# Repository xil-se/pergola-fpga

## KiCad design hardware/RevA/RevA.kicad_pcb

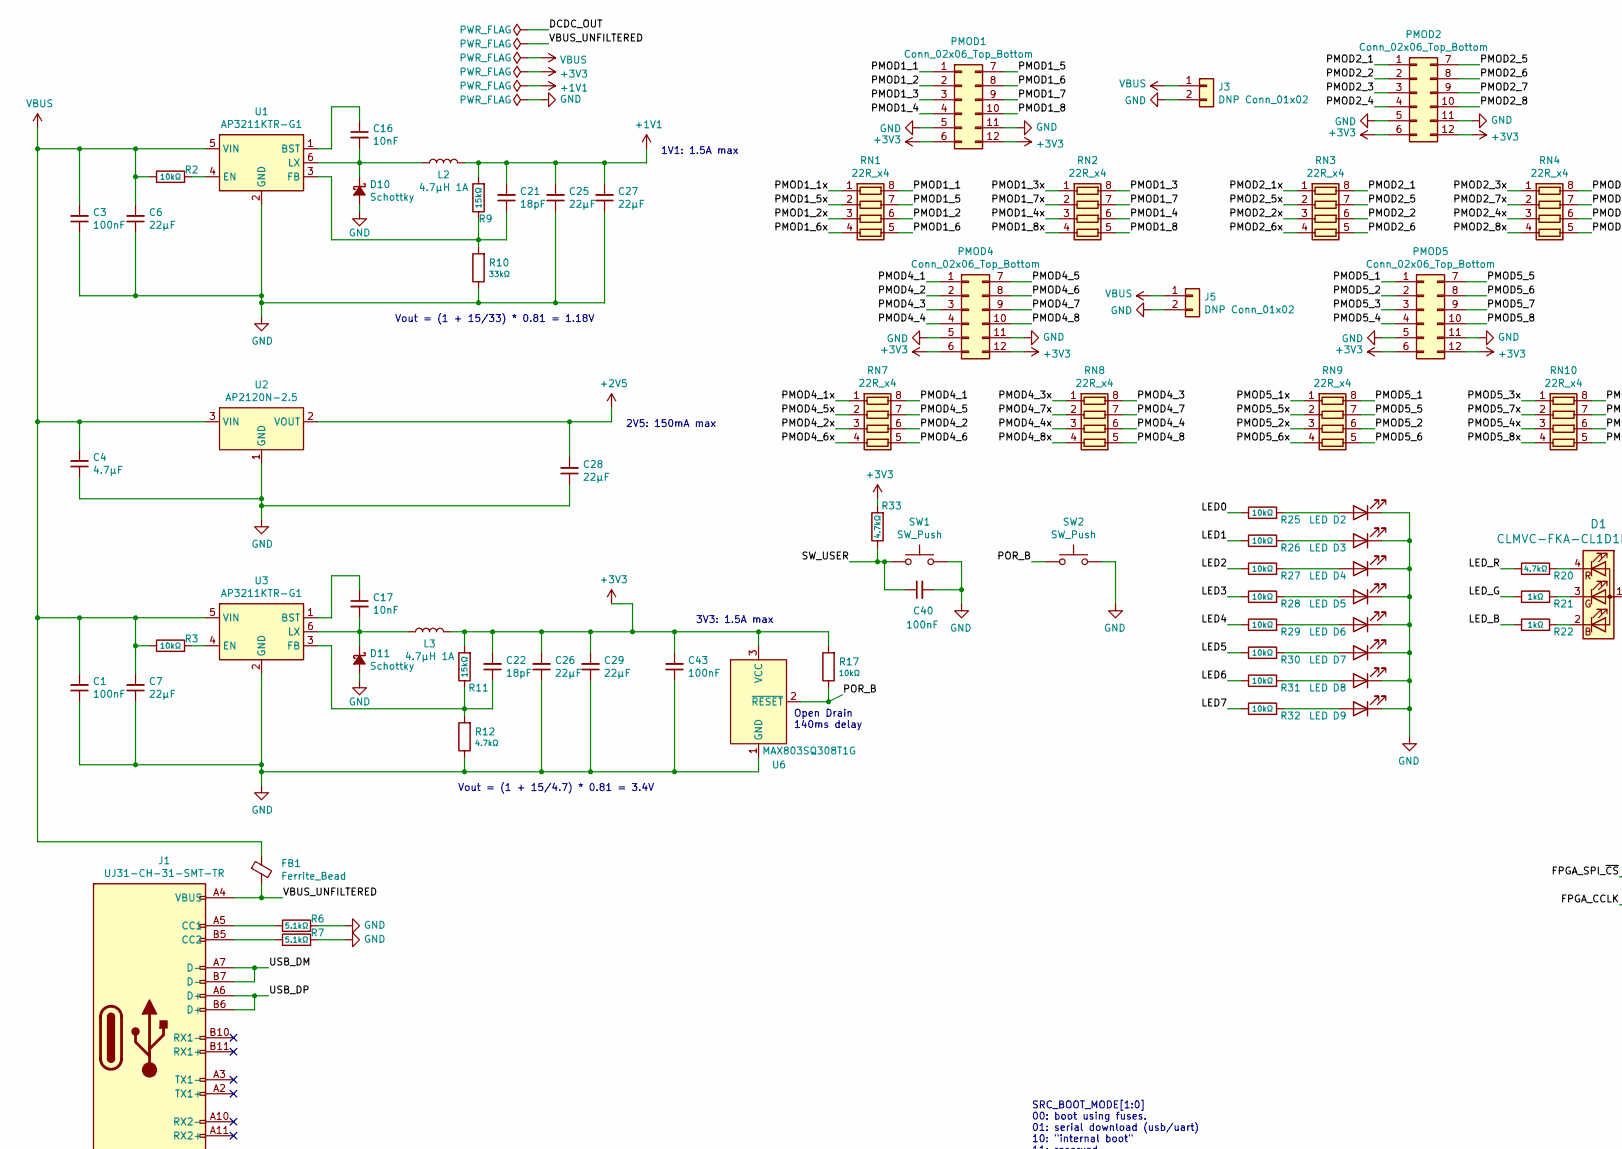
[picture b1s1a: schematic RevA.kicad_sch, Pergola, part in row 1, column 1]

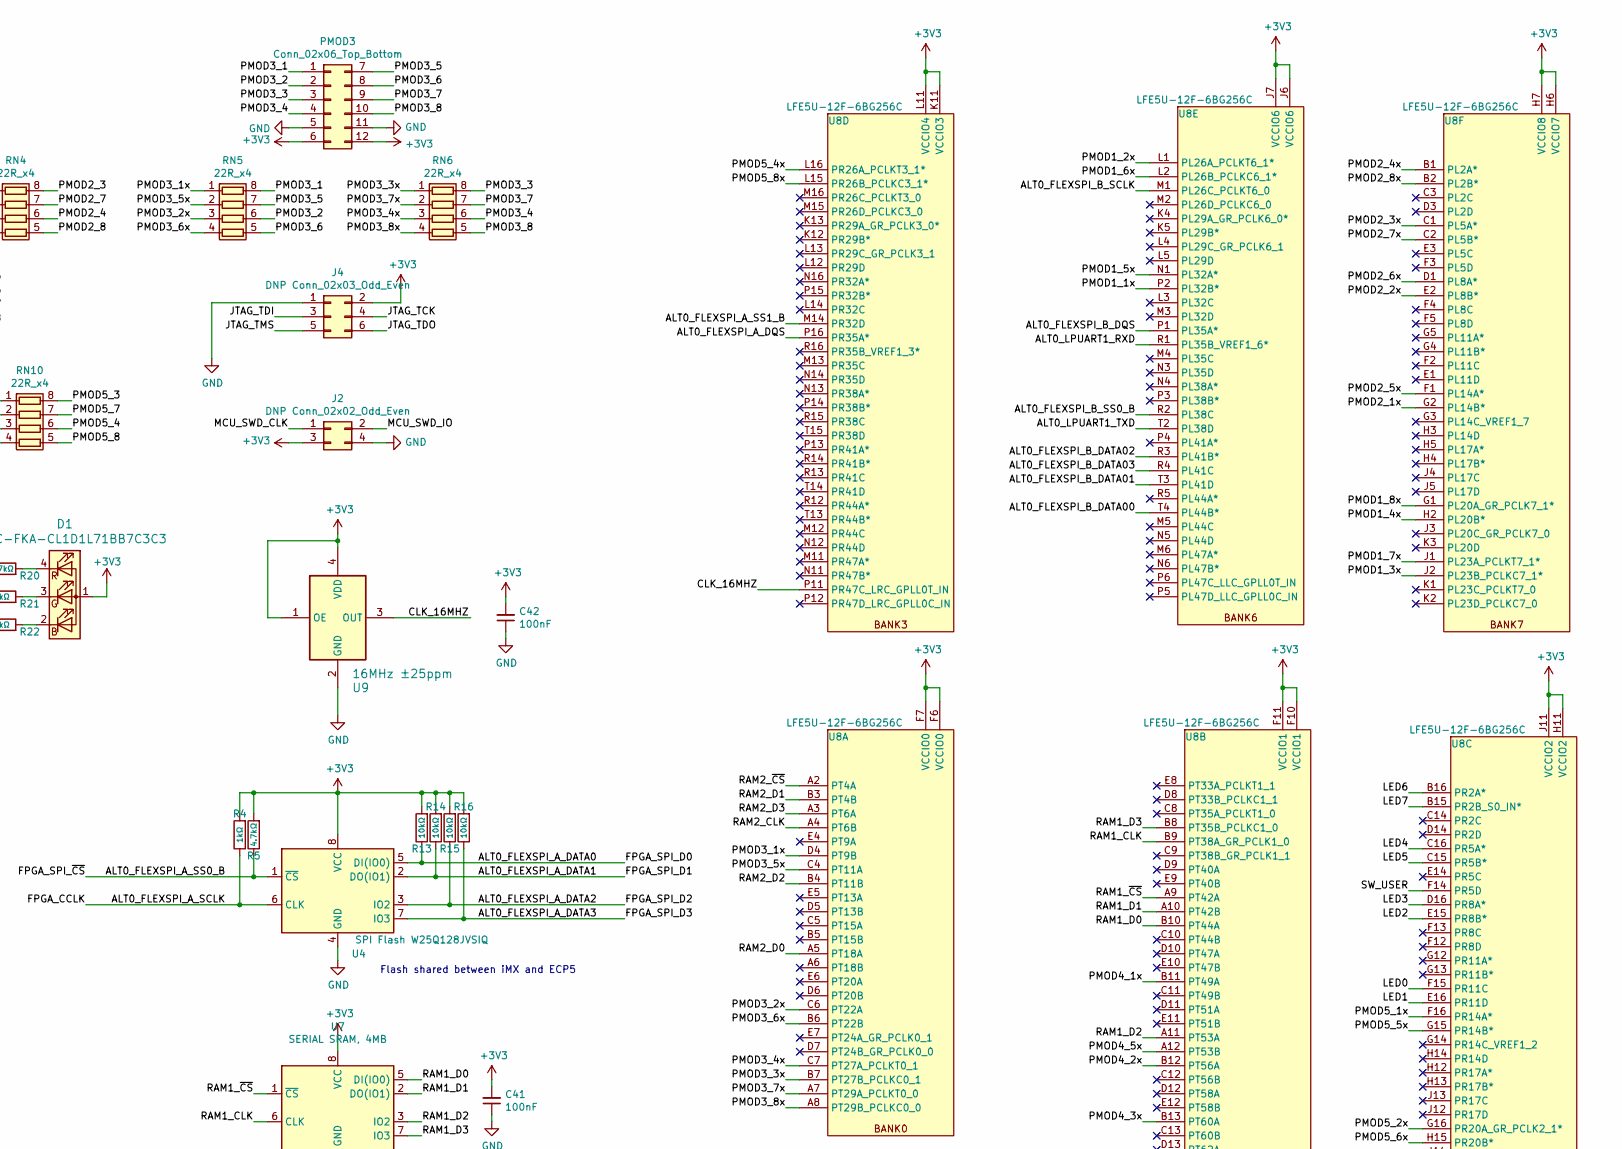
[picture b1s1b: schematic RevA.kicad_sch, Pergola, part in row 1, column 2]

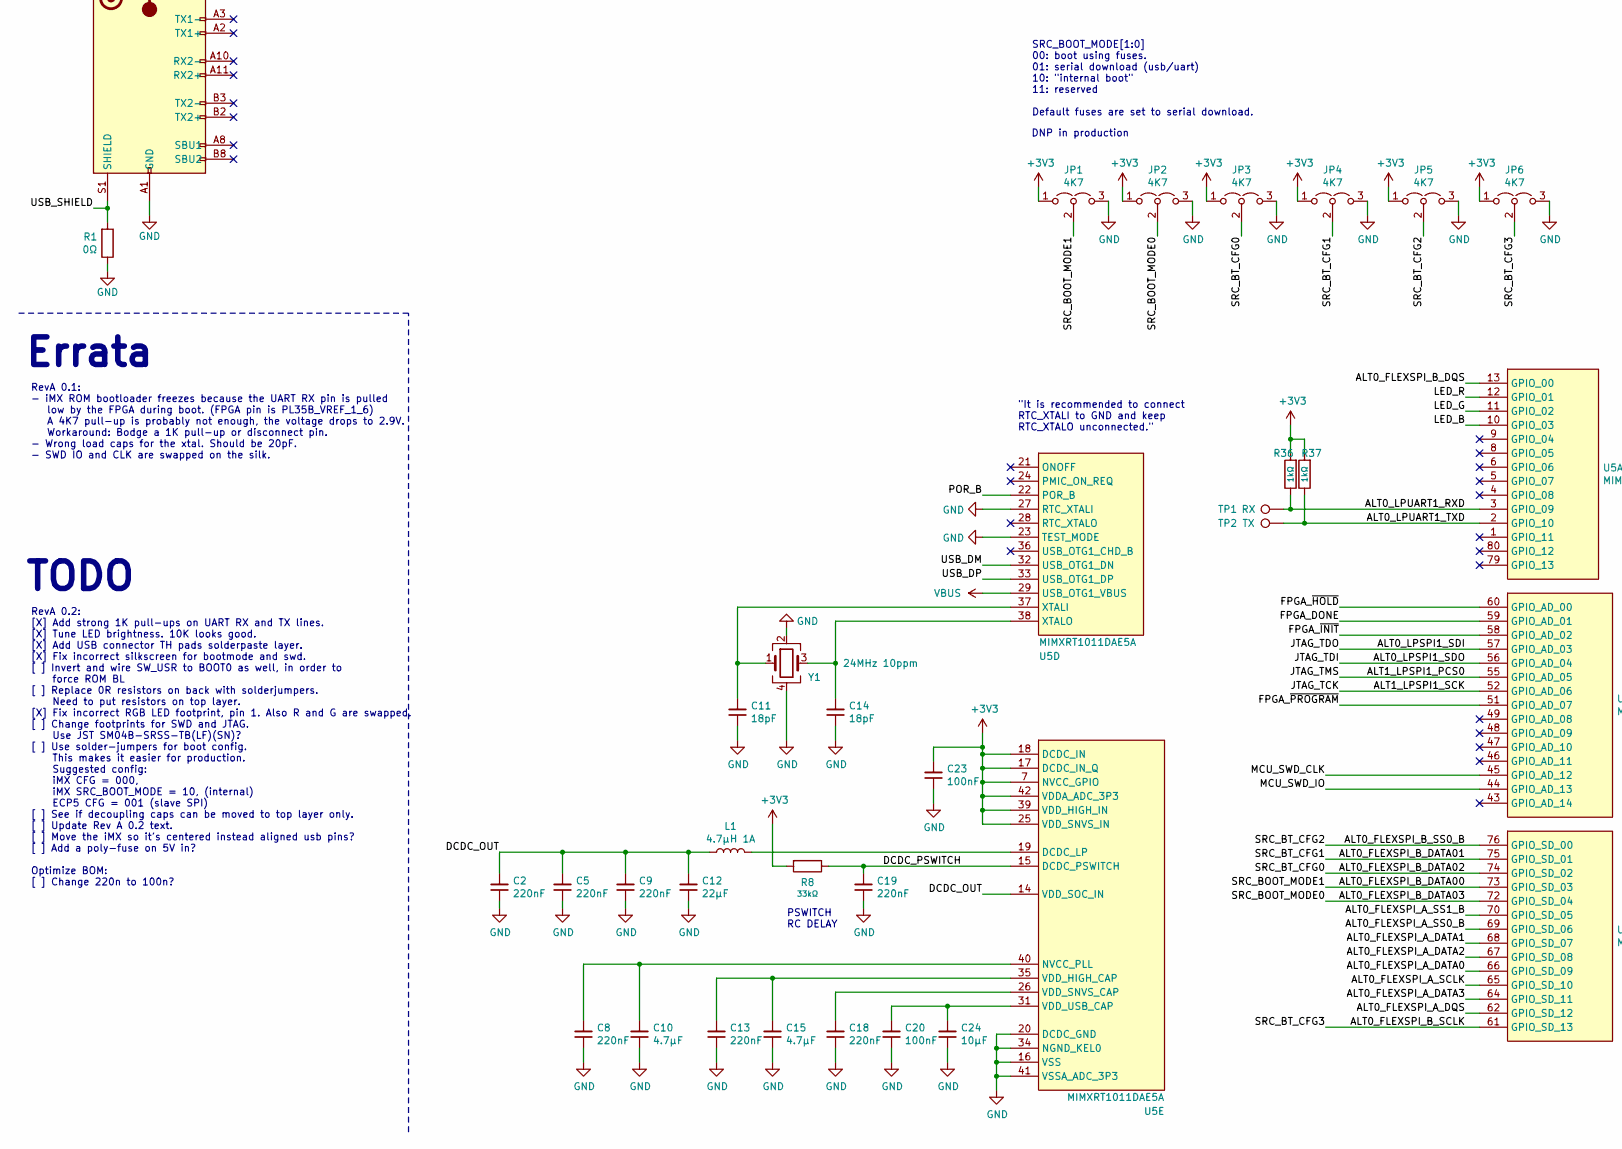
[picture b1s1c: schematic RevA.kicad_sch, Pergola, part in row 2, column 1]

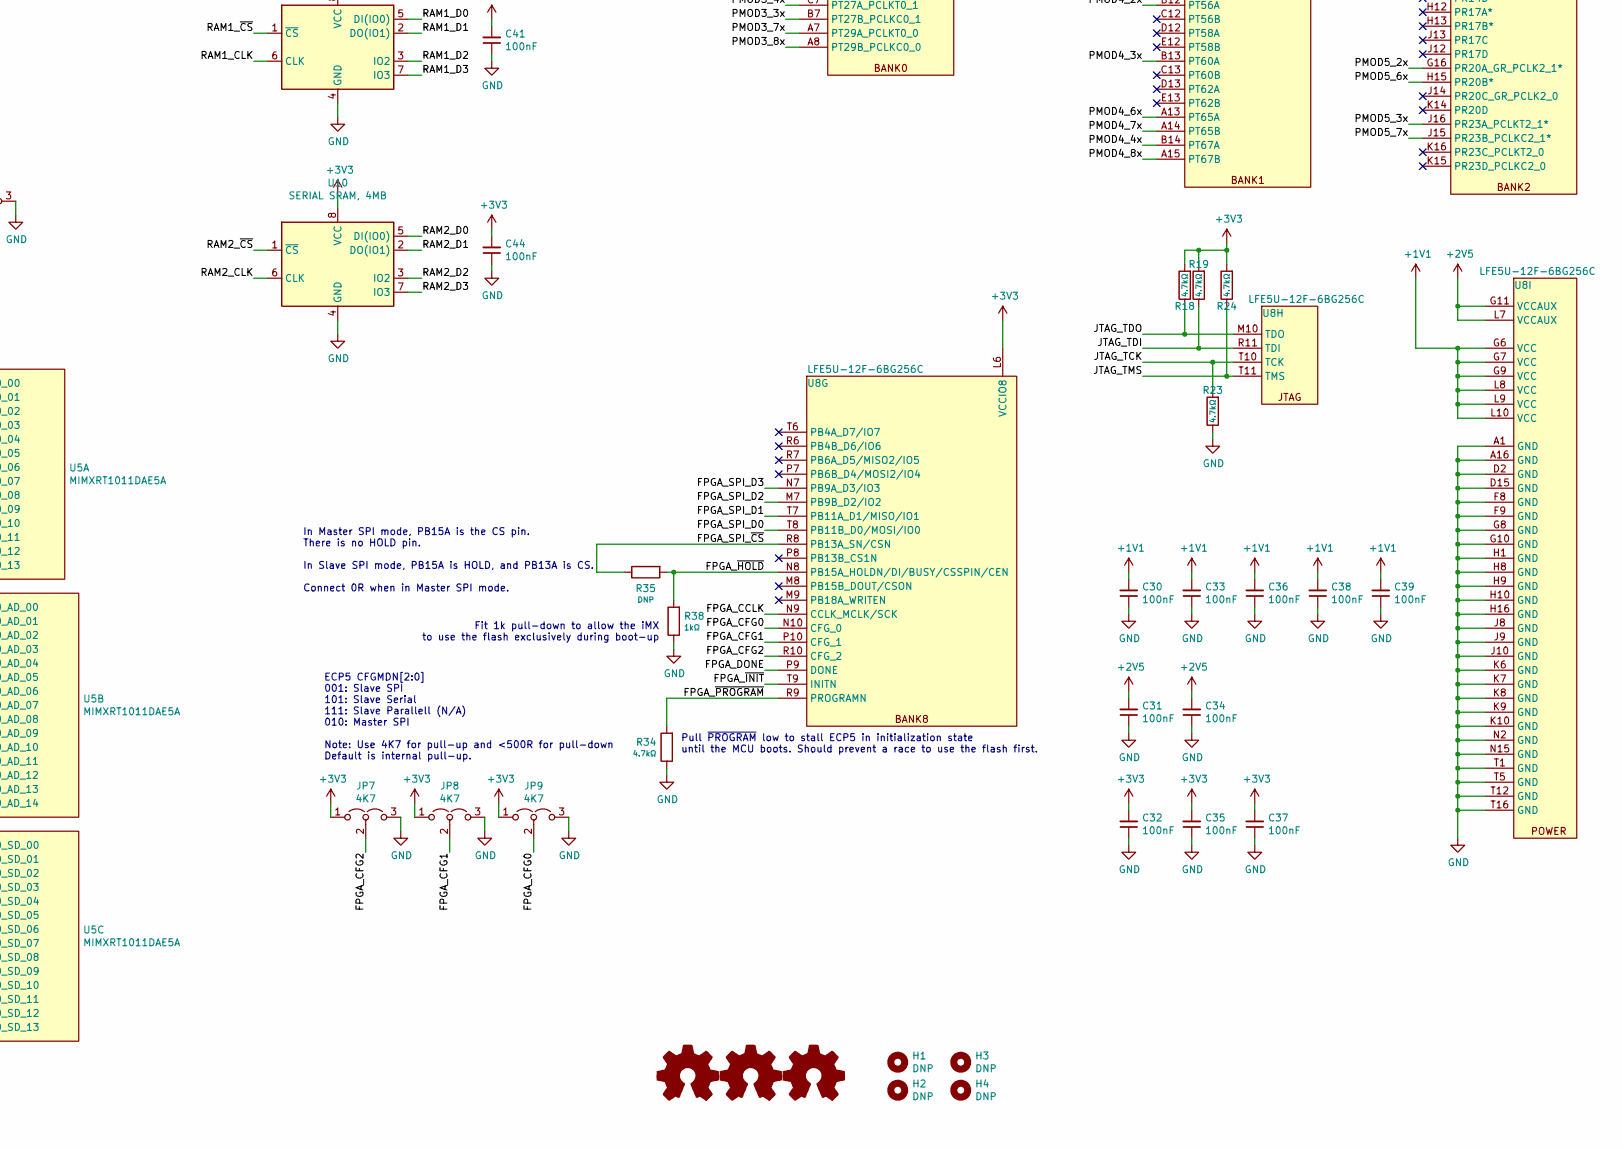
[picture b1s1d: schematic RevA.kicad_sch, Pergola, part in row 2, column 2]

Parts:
C1, C3, C20, C23, C30, C31, C32, C33, C34, C35, C36, C37, C38, C39, C40, C41, C42, C43, C44: 100nF; C_0402_1005Metric
C2, C5, C8, C9, C13, C18, C19: 220nF; C_0402_1005Metric
C4, C10, C15: 4.7µF; C_0402_1005Metric
C6, C7, C12, C25, C26, C27, C28, C29: 22µF; C_0805_2012Metric; Digikey 490-GRM219R61C226ME15KCT-ND
C11, C14, C21, C22: 18pF; C_0402_1005Metric
C16, C17: 10nF; C_0402_1005Metric
C24: 10µF; C_0402_1005Metric
D1: CLMVC-FKA-CL1D1L71BB7C3C3; LED_Cree-PLCC4_2x2mm_CW; Mouser 941-CLMVCFKACL1D1L71
D2, D3, D4, D5, D6, D7, D8, D9: LED; LED_0603_1608Metric; Digikey 732-4978-1-ND
D10, D11: Schottky; D_SOD-323F; Digikey 1727-3852-1-ND
FB1: Ferrite_Bead; L_0805_2012Metric; Digikey 490-5987-1-ND
H1, H2, H3, H4: DNP; MountingHole_3.5mm
J1: UJ31-CH-31-SMT-TR; CUI_UJ31-CH-312-SMT-TR; Digikey 102-4485-1-ND
J2: DNP Conn_02x02_Odd_Even; PinHeader_2x02_P2.54mm_Vertical_SMD
J3, J5: DNP Conn_01x02; PinSocket_1x02_P2.54mm_Vertical
J4: DNP Conn_02x03_Odd_Even; PinHeader_2x03_P2.54mm_Vertical_SMD
JP1, JP2, JP3, JP4, JP5, JP6, JP7, JP8, JP9: 4K7; JP_3_0402_1005Metric
L1, L2, L3: 4.7µH 1A; L_1008_1210; Digikey 490-18407-1-ND
LOGO1: Logo_Open_Hardware_Small; OSHW-Logo_5.7x6mm_SilkScreen
LOGO2: Logo_Open_Hardware_Small; logo
LOGO3: Logo_Open_Hardware_Small; xil_logo_new
PMOD1, PMOD2, PMOD3, PMOD4, PMOD5: Conn_02x06_Top_Bottom; PMOD_Socket_2x06_P2.54mm_Horizontal; Digikey SAM1224-06-ND
R1: 0Ω; R_0402_1005Metric
R2, R3, R13, R14, R15, R16, R17, R25, R26, R27, R28, R29, R30, R31, R32: 10kΩ; R_0402_1005Metric
R4, R21, R22, R36, R37, R38: 1kΩ; R_0402_1005Metric
R5, R12, R18, R19, R20, R23, R24, R33, R34: 4.7kΩ; R_0402_1005Metric
R6, R7: 5.1kΩ; R_0402_1005Metric
R8, R10: 33kΩ; R_0402_1005Metric
R9, R11: 15kΩ; R_0402_1005Metric
R35: DNP; R_0402_1005Metric
RN1, RN2, RN3, RN4, RN5, RN6, RN7, RN8, RN9, RN10: 22R_x4; R_Array_Convex_4x0402; Digikey Y7220CT-ND
SW1, SW2: SW_Push; SW_SPST_FSMSM; Digikey CKN12329-1-ND
TP1: RX; TestPoint_Pad_D1.0mm
TP2: TX; TestPoint_Pad_D1.0mm
U1, U3: AP3211KTR-G1; SOT-23-6; Digikey AP3211KTR-G1DICT-ND
U2: AP2120N-2.5; SOT-23; Digikey AP2120N-2.5TRG1DICT-ND
U4: SPI Flash W25Q128JVSIQ; SOA008-150-208mil; Digikey W25Q128JVSIQCT-ND
U5: MIMXRT1011DAE5A; LQFP-80_12x12mm_P0.5mm; Digikey 568-MIMXRT1011DAE5A-ND
U6: MAX803SQ308T1G; SOT-323_SC-70; Digikey MAX803SQ308T1GOSCT-ND
U7, U10: SERIAL SRAM, 4MB; SOIC-8_3.9x4.9mm_P1.27mm; Mouser 870-62WS5128FBLL2NIT
U8: LFE5U-12F-6BG256C; cabga256; Mouser 842-LFE5U12F6BG256C
U9: 16MHz ±25ppm; Crystal_SMD_3225-4Pin_3.2x2.5mm; Mouser 520-3225MV-160-CNT
Y1: 24MHz 10ppm; Crystal_SMD_3225-4Pin_3.2x2.5mm; Mouser 732-TX325-24F20G-AC3

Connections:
+1V1: C21.2, C25.2, C27.2, C30.2, C33.2, C36.2, C38.2, C39.2, L2.2, R9.2, U8.G6 (VCC), U8.G7 (VCC), U8.G9 (VCC), U8.L8 (VCC), U8.L9 (VCC), U8.L10 (VCC)
+2V5: C28.2, C31.2, C34.2, U2.2 (VOUT), U8.G11 (VCCAUX), U8.L7 (VCCAUX)
+3V3: C22.2, C23.2, C26.2, C29.2, C32.2, C35.2, C37.2, C41.2, C42.2, C43.2, C44.2, D1.1 (A), J2.3, J4.2, JP1.1 (A), JP2.1 (A), JP3.1 (A), JP4.1 (A), JP5.1 (A), JP6.1 (A), JP7.1 (A), JP8.1 (A), JP9.1 (A), L3.2, PMOD1.6, PMOD1.12, PMOD2.6, PMOD2.12, PMOD3.6, PMOD3.12, PMOD4.6, PMOD4.12, PMOD5.6, PMOD5.12, R4.2, R5.2, R8.2, R11.2, R13.2, R14.2, R15.2, R16.2, R17.2, R18.2, R19.2, R24.2, R33.2, R36.2, R37.2, U4.8 (VCC), U5.7 (NVCC_GPIO), U5.17 (DCDC_IN_Q), U5.18 (DCDC_IN), U5.25 (VDD_SNVS_IN), U5.39 (VDD_HIGH_IN), U5.42 (VDDA_ADC_3P3), U5.50 (NVCC_GPIO), U5.63 (NVCC_GPIO), U5.71 (NVCC_GPIO), U6.3 (VCC), U7.8 (VCC), U8.F6 (VCCIO0), U8.F7 (VCCIO0), U8.F10 (VCCIO1), U8.F11 (VCCIO1), U8.H6 (VCCIO7), U8.H7 (VCCIO8), U8.H11 (VCCIO2), U8.J6 (VCCIO6), U8.J7 (VCCIO6), U8.J11 (VCCIO2), U8.K11 (VCCIO3), U8.L6 (VCCIO8), U8.L11 (VCCIO4), U9.1 (OE), U9.4 (VDD), U10.8 (VCC)
/ALT0_FLEXSPI_A_DATA0: R13.1, U4.5 (DI(IO0)), U5.66 (GPIO_SD_09), U8.T8 (PB11B_D0/MOSI/IO0)
/ALT0_FLEXSPI_A_DATA1: R14.1, U4.2 (DO(IO1)), U5.68 (GPIO_SD_07), U8.T7 (PB11A_D1/MISO/IO1)
/ALT0_FLEXSPI_A_DATA2: R15.1, U4.3 (IO2), U5.67 (GPIO_SD_08), U8.M7 (PB9B_D2/IO2)
/ALT0_FLEXSPI_A_DATA3: R16.1, U4.7 (IO3), U5.64 (GPIO_SD_11), U8.N7 (PB9A_D3/IO3)
/ALT0_FLEXSPI_A_DQS: U5.62 (GPIO_SD_12), U8.P16 (PR35A*)
/ALT0_FLEXSPI_A_SCLK: R4.1, U4.6 (CLK), U5.65 (GPIO_SD_10), U8.N9 (CCLK_MCLK/SCK)
/ALT0_FLEXSPI_A_SS0_B: R5.1, R35.1, U4.1 (~CS), U5.69 (GPIO_SD_06), U8.R8 (PB13A_SN/CSN)
/ALT0_FLEXSPI_A_SS1_B: U5.70 (GPIO_SD_05), U8.M14 (PR32D)
/ALT0_FLEXSPI_B_DATA00: JP1.2 (C), U5.73 (GPIO_SD_03), U8.T4 (PL44B*)
/ALT0_FLEXSPI_B_DATA01: JP4.2 (C), U5.75 (GPIO_SD_01), U8.T3 (PL41D)
/ALT0_FLEXSPI_B_DATA02: JP3.2 (C), U5.74 (GPIO_SD_02), U8.R3 (PL41B*)
/ALT0_FLEXSPI_B_DATA03: JP2.2 (C), U5.72 (GPIO_SD_04), U8.R4 (PL41C)
/ALT0_FLEXSPI_B_DQS: U5.13 (GPIO_00), U8.P1 (PL35A*)
/ALT0_FLEXSPI_B_SCLK: JP6.2 (C), U5.61 (GPIO_SD_13), U8.M1 (PL26C_PCLKT6_0)
/ALT0_FLEXSPI_B_SS0_B: JP5.2 (C), U5.76 (GPIO_SD_00), U8.R2 (PL38C)
/ALT0_LPSPI1_SDI: J4.6, R18.1, U5.57 (GPIO_AD_03), U8.M10 (TDO)
/ALT0_LPSPI1_SDO: J4.3, R19.1, U5.56 (GPIO_AD_04), U8.R11 (TDI)
/ALT0_LPUART1_RXD: R36.1, TP1.1, U5.3 (GPIO_09), U8.R1 (PL35B_VREF1_6*)
/ALT0_LPUART1_TXD: R37.1, TP2.1, U5.2 (GPIO_10), U8.T2 (PL38D)
/ALT1_LPSPI1_PCS0: J4.5, R24.1, U5.55 (GPIO_AD_05), U8.T11 (TMS)
/ALT1_LPSPI1_SCK: J4.4, R23.2, U5.52 (GPIO_AD_06), U8.T10 (TCK)
/CLK_16MHZ: U8.P11 (PR47C_LRC_GPLL0T_IN), U9.3 (OUT)
/DCDC_OUT: C2.2, C5.2, C9.2, C12.2, L1.1, U5.14 (VDD_SOC_IN), U5.53 (VDD_SOC_IN), U5.77 (VDD_SOC_IN)
/DCDC_PSWITCH: C19.2, R8.1, U5.15 (DCDC_PSWITCH)
/FPGA_CFG0: JP9.2 (C), U8.N10 (CFG_0)
/FPGA_CFG1: JP8.2 (C), U8.P10 (CFG_1)
/FPGA_CFG2: JP7.2 (C), U8.R10 (CFG_2)
/FPGA_DONE: U5.59 (GPIO_AD_01), U8.P9 (DONE)
/FPGA_~HOLD: R35.2, R38.2, U5.60 (GPIO_AD_00), U8.N8 (PB15A_HOLDN/DI/BUSY/CSSPIN/CEN)
/FPGA_~INIT: U5.58 (GPIO_AD_02), U8.T9 (INITN)
/FPGA_~PROGRAM: R34.2, U5.51 (GPIO_AD_07), U8.R9 (PROGRAMN)
/LED0: R25.1, U8.F15 (PR11C)
/LED1: R26.1, U8.E16 (PR11D)
/LED2: R27.1, U8.E15 (PR8B*)
/LED3: R28.1, U8.D16 (PR8A*)
/LED4: R29.1, U8.C16 (PR5A*)
/LED5: R30.1, U8.C15 (PR5B*)
/LED6: R31.1, U8.B16 (PR2A*)
/LED7: R32.1, U8.B15 (PR2B_S0_IN*)
/LED_B: R22.1, U5.10 (GPIO_03)
/LED_G: R21.1, U5.11 (GPIO_02)
/LED_R: R20.1, U5.12 (GPIO_01)
/MCU_SWD_CLK: J2.1, U5.45 (GPIO_AD_12)
/MCU_SWD_IO: J2.2, U5.44 (GPIO_AD_13)
/PMOD1_1: PMOD1.1, RN1.8 (R1.2)
/PMOD1_1x: RN1.1 (R1.1), U8.P2 (PL32B*)
/PMOD1_2: PMOD1.2, RN1.6 (R3.2)
/PMOD1_2x: RN1.3 (R3.1), U8.L1 (PL26A_PCLKT6_1*)
/PMOD1_3: PMOD1.3, RN2.8 (R1.2)
/PMOD1_3x: RN2.1 (R1.1), U8.J2 (PL23B_PCLKC7_1*)
/PMOD1_4: PMOD1.4, RN2.6 (R3.2)
/PMOD1_4x: RN2.3 (R3.1), U8.H2 (PL20B*)
/PMOD1_5: PMOD1.7, RN1.7 (R2.2)
/PMOD1_5x: RN1.2 (R2.1), U8.N1 (PL32A*)
/PMOD1_6: PMOD1.8, RN1.5 (R4.2)
/PMOD1_6x: RN1.4 (R4.1), U8.L2 (PL26B_PCLKC6_1*)
/PMOD1_7: PMOD1.9, RN2.7 (R2.2)
/PMOD1_7x: RN2.2 (R2.1), U8.J1 (PL23A_PCLKT7_1*)
/PMOD1_8: PMOD1.10, RN2.5 (R4.2)
/PMOD1_8x: RN2.4 (R4.1), U8.G1 (PL20A_GR_PCLK7_1*)
/PMOD2_1: PMOD2.1, RN3.8 (R1.2)
/PMOD2_1x: RN3.1 (R1.1), U8.G2 (PL14B*)
/PMOD2_2: PMOD2.2, RN3.6 (R3.2)
/PMOD2_2x: RN3.3 (R3.1), U8.E2 (PL8B*)
/PMOD2_3: PMOD2.3, RN4.8 (R1.2)
/PMOD2_3x: RN4.1 (R1.1), U8.C1 (PL5A*)
/PMOD2_4: PMOD2.4, RN4.6 (R3.2)
/PMOD2_4x: RN4.3 (R3.1), U8.B1 (PL2A*)
/PMOD2_5: PMOD2.7, RN3.7 (R2.2)
/PMOD2_5x: RN3.2 (R2.1), U8.F1 (PL14A*)
/PMOD2_6: PMOD2.8, RN3.5 (R4.2)
/PMOD2_6x: RN3.4 (R4.1), U8.D1 (PL8A*)
/PMOD2_7: PMOD2.9, RN4.7 (R2.2)
/PMOD2_7x: RN4.2 (R2.1), U8.C2 (PL5B*)
/PMOD2_8: PMOD2.10, RN4.5 (R4.2)
/PMOD2_8x: RN4.4 (R4.1), U8.B2 (PL2B*)
/PMOD3_1: PMOD3.1, RN5.8 (R1.2)
/PMOD3_1x: RN5.1 (R1.1), U8.D4 (PT9B)
/PMOD3_2: PMOD3.2, RN5.6 (R3.2)
/PMOD3_2x: RN5.3 (R3.1), U8.C6 (PT22A)
/PMOD3_3: PMOD3.3, RN6.8 (R1.2)
/PMOD3_3x: RN6.1 (R1.1), U8.B7 (PT27B_PCLKC0_1)
/PMOD3_4: PMOD3.4, RN6.6 (R3.2)
/PMOD3_4x: RN6.3 (R3.1), U8.C7 (PT27A_PCLKT0_1)
/PMOD3_5: PMOD3.7, RN5.7 (R2.2)
/PMOD3_5x: RN5.2 (R2.1), U8.C4 (PT11A)
/PMOD3_6: PMOD3.8, RN5.5 (R4.2)
/PMOD3_6x: RN5.4 (R4.1), U8.B6 (PT22B)
/PMOD3_7: PMOD3.9, RN6.7 (R2.2)
/PMOD3_7x: RN6.2 (R2.1), U8.A7 (PT29A_PCLKT0_0)
/PMOD3_8: PMOD3.10, RN6.5 (R4.2)
/PMOD3_8x: RN6.4 (R4.1), U8.A8 (PT29B_PCLKC0_0)
/PMOD4_1: PMOD4.1, RN7.8 (R1.2)
/PMOD4_1x: RN7.1 (R1.1), U8.B11 (PT49A)
/PMOD4_2: PMOD4.2, RN7.6 (R3.2)
/PMOD4_2x: RN7.3 (R3.1), U8.B12 (PT56A)
/PMOD4_3: PMOD4.3, RN8.8 (R1.2)
/PMOD4_3x: RN8.1 (R1.1), U8.B13 (PT60A)
/PMOD4_4: PMOD4.4, RN8.6 (R3.2)
/PMOD4_4x: RN8.3 (R3.1), U8.B14 (PT67A)
/PMOD4_5: PMOD4.7, RN7.7 (R2.2)
/PMOD4_5x: RN7.2 (R2.1), U8.A12 (PT53B)
/PMOD4_6: PMOD4.8, RN7.5 (R4.2)
/PMOD4_6x: RN7.4 (R4.1), U8.A13 (PT65A)
/PMOD4_7: PMOD4.9, RN8.7 (R2.2)
/PMOD4_7x: RN8.2 (R2.1), U8.A14 (PT65B)
/PMOD4_8: PMOD4.10, RN8.5 (R4.2)
/PMOD4_8x: RN8.4 (R4.1), U8.A15 (PT67B)
/PMOD5_1: PMOD5.1, RN9.8 (R1.2)
/PMOD5_1x: RN9.1 (R1.1), U8.F16 (PR14A*)
/PMOD5_2: PMOD5.2, RN9.6 (R3.2)
/PMOD5_2x: RN9.3 (R3.1), U8.G16 (PR20A_GR_PCLK2_1*)
/PMOD5_3: PMOD5.3, RN10.8 (R1.2)
/PMOD5_3x: RN10.1 (R1.1), U8.J16 (PR23A_PCLKT2_1*)
/PMOD5_4: PMOD5.4, RN10.6 (R3.2)
/PMOD5_4x: RN10.3 (R3.1), U8.L16 (PR26A_PCLKT3_1*)
/PMOD5_5: PMOD5.7, RN9.7 (R2.2)
/PMOD5_5x: RN9.2 (R2.1), U8.G15 (PR14B*)
/PMOD5_6: PMOD5.8, RN9.5 (R4.2)
/PMOD5_6x: RN9.4 (R4.1), U8.H15 (PR20B*)
/PMOD5_7: PMOD5.9, RN10.7 (R2.2)
/PMOD5_7x: RN10.2 (R2.1), U8.J15 (PR23B_PCLKC2_1*)
/PMOD5_8: PMOD5.10, RN10.5 (R4.2)
/PMOD5_8x: RN10.4 (R4.1), U8.L15 (PR26B_PCLKC3_1*)
/POR_B: R17.1, SW2.1, U5.22 (POR_B), U6.2 (~RESET~)
/RAM1_CLK: U7.6 (CLK), U8.B9 (PT38A_GR_PCLK1_0)
/RAM1_D0: U7.5 (DI(IO0)), U8.B10 (PT44A)
/RAM1_D1: U7.2 (DO(IO1)), U8.A10 (PT42B)
/RAM1_D2: U7.3 (IO2), U8.A11 (PT53A)
/RAM1_D3: U7.7 (IO3), U8.B8 (PT35B_PCLKC1_0)
/RAM1_~CS~: U7.1 (~CS), U8.A9 (PT42A)
/RAM2_CLK: U8.A4 (PT6B), U10.6 (CLK)
/RAM2_D0: U8.A5 (PT18A), U10.5 (DI(IO0))
/RAM2_D1: U8.B3 (PT4B), U10.2 (DO(IO1))
/RAM2_D2: U8.B4 (PT11B), U10.3 (IO2)
/RAM2_D3: U8.A3 (PT6A), U10.7 (IO3)
/RAM2_~CS~: U8.A2 (PT4A), U10.1 (~CS)
/SW_USER: C40.1, R33.1, SW1.1, U8.F14 (PR5D)
/USB_DM: J1.A7 (D-), J1.B7 (D-), U5.32 (USB_OTG1_DN)
/USB_DP: J1.A6 (D+), J1.B6 (D+), U5.33 (USB_OTG1_DP)
/USB_SHIELD: J1.S1 (SHIELD), R1.2
/VBUS_UNFILTERED: FB1.2, J1.A4 (VBUS), J1.A9 (VBUS), J1.B4 (VBUS), J1.B9 (VBUS)
GND: C1.1, C2.1, C3.1, C4.1, C5.1, C6.1, C7.1, C8.1, C9.1, C10.1, C11.1, C12.1, C13.1, C14.1, C15.1, C18.1, C19.1, C20.1, C23.1, C24.1, C25.1, C26.1, C27.1, C28.1, C29.1, C30.1, C31.1, C32.1, C33.1, C34.1, C35.1, C36.1, C37.1, C38.1, C39.1, C40.2, C41.1, C42.1, C43.1, C44.1, D2.1 (K), D3.1 (K), D4.1 (K), D5.1 (K), D6.1 (K), D7.1 (K), D8.1 (K), D9.1 (K), D10.2 (A), D11.2 (A), J1.A1 (GND), J1.A12 (GND), J1.B1 (GND), J1.B12 (GND), J2.4, J3.2, J4.1, J5.2, JP1.3 (B), JP2.3 (B), JP3.3 (B), JP4.3 (B), JP5.3 (B), JP6.3 (B), JP7.3 (B), JP8.3 (B), JP9.3 (B), PMOD1.5, PMOD1.11, PMOD2.5, PMOD2.11, PMOD3.5, PMOD3.11, PMOD4.5, PMOD4.11, PMOD5.5, PMOD5.11, R1.1, R6.2, R7.2, R10.1, R12.1, R23.1, R34.1, R38.1, SW1.2, SW2.2, U1.2 (GND), U2.1 (GND), U3.2 (GND), U4.4 (GND), U5.16 (VSS), U5.20 (DCDC_GND), U5.23 (TEST_MODE), U5.27 (RTC_XTALI), U5.30 (VSS), U5.34 (NGND_KEL0), U5.41 (VSSA_ADC_3P3), U5.54 (VSS), U5.78 (VSS), U6.1 (GND), U7.4 (GND), U8.A1 (GND), U8.A16 (GND), U8.D2 (GND), U8.D15 (GND), U8.F8 (GND), U8.F9 (GND), U8.G8 (GND), U8.G10 (GND), U8.H1 (GND), U8.H8 (GND), U8.H9 (GND), U8.H10 (GND), U8.H16 (GND), U8.J8 (GND), U8.J9 (GND), U8.J10 (GND), U8.K6 (GND), U8.K7 (GND), U8.K8 (GND), U8.K9 (GND), U8.K10 (GND), U8.N2 (GND), U8.N15 (GND), U8.T1 (GND), U8.T5 (GND), U8.T12 (GND), U8.T16 (GND), U9.2 (GND), U10.4 (GND), Y1.2, Y1.4
unnamed: C8.2, C10.2, U5.40 (NVCC_PLL)
unnamed: C11.2, U5.37 (XTALI), Y1.1
unnamed: C13.2, C15.2, U5.35 (VDD_HIGH_CAP)
unnamed: C14.2, U5.38 (XTALO), Y1.3
unnamed: C16.1, U1.1 (BST)
unnamed: C16.2, D10.1 (K), L2.1, U1.6 (LX)
unnamed: C17.1, U3.1 (BST)
unnamed: C17.2, D11.1 (K), L3.1, U3.6 (LX)
unnamed: C18.2, U5.26 (VDD_SNVS_CAP)
unnamed: C20.2, C24.2, U5.31 (VDD_USB_CAP)
unnamed: C21.1, R9.1, R10.2, U1.3 (FB)
unnamed: C22.1, R11.1, R12.2, U3.3 (FB)
unnamed: D1.2 (BK), R22.2
unnamed: D1.3 (GK), R21.2
unnamed: D1.4 (RK), R20.2
unnamed: D2.2 (A), R25.2
unnamed: D3.2 (A), R26.2
unnamed: D4.2 (A), R27.2
unnamed: D5.2 (A), R28.2
unnamed: D6.2 (A), R29.2
unnamed: D7.2 (A), R30.2
unnamed: D8.2 (A), R31.2
unnamed: D9.2 (A), R32.2
unnamed: J1.A5 (CC1), R6.1
unnamed: J1.B5 (CC2), R7.1
unnamed: L1.2, U5.19 (DCDC_LP)
unnamed: R2.2, U1.4 (EN)
unnamed: R3.2, U3.4 (EN)
VBUS: C1.2, C3.2, C4.2, C6.2, C7.2, FB1.1, J3.1, J5.1, R2.1, R3.1, U1.5 (VIN), U2.3 (VIN), U3.5 (VIN), U5.29 (USB_OTG1_VBUS)

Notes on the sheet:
Errata
TODO
RevA 0.1: - iMX ROM bootloader freezes because the UART RX pin is pulled low by the FPGA during boot. (FPGA pin is PL35B_VREF_1_6) A 4K7 pull-up is probably not enough, the voltage drops to 2.9V. Workaround: Bodge a 1K pull-up or disconnect pin. - Wrong load caps for the xtal. Should be 20pF. - SWD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
RevA 0.2: [X] Add strong 1K pull-ups on UART RX and TX lines. [X] Tune LED brightness. 10K looks good. [X] Add USB connector TH pads solderpaste layer. [X] Fix incorrect silkscreen for bootmode and swd. [ ] Invert and wire SW_USR to BOOT0 as well, in order to force ROM BL [ ] Replace 0R resistors o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
Vout = (1 + 15/33) * 0.81 = 1.18V
Vout = (1 + 15/4.7) * 0.81 = 3.4V
2V5: 150mA max
1V1: 1.5A max
3V3: 1.5A max
PSWITCH RC DELAY
Open Drain 140ms delay
"It is recommended to connect RTC_XTALI to GND and keep RTC_XTALO unconnected."
SRC_BOOT_MODE[1:0] 00: boot using fuses. 01: serial download (usb/uart) 10: "internal boot" 11: reserved Default fuses are set to serial download.
DNP in production
In Master SPI mode, PB15A is the CS pin. There is no HOLD pin. In Slave SPI mode, PB15A is HOLD, and PB13A is CS. Connect 0R when in Master SPI mode.
ECP5 CFGMDN[2:0] 001: Slave SPI 101: Slave Serial 111: Slave Parallell (N/A) 010: Master SPI Note: Use 4K7 for pull-up and <500R for pull-down Default is internal pull-up.
Flash shared between iMX and ECP5
Fit 1k pull-down to allow the iMX to use the flash exclusively during boot-up
Pull ~PROGRAM~ low to stall ECP5 in initialization state until the MCU boots. Should prevent a race to use the flash first.

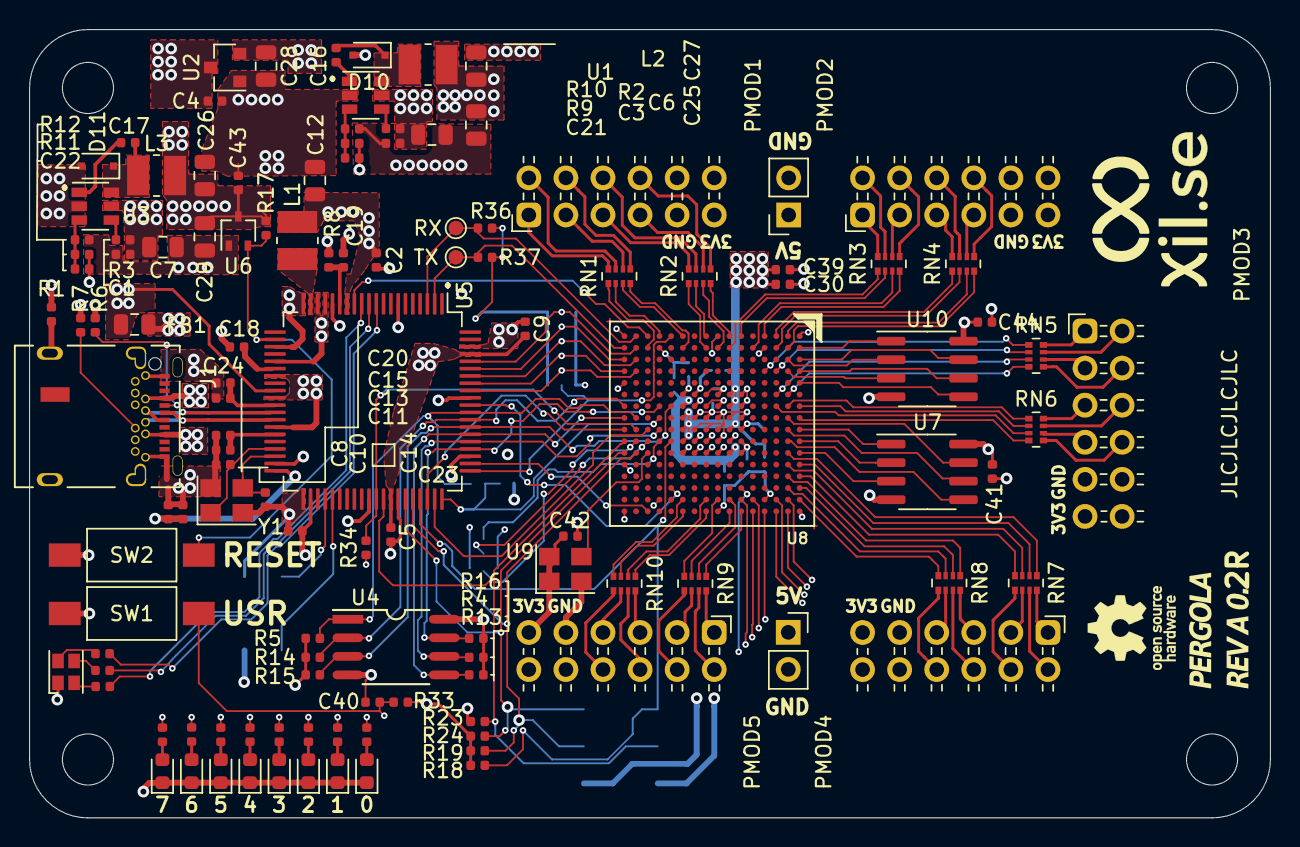
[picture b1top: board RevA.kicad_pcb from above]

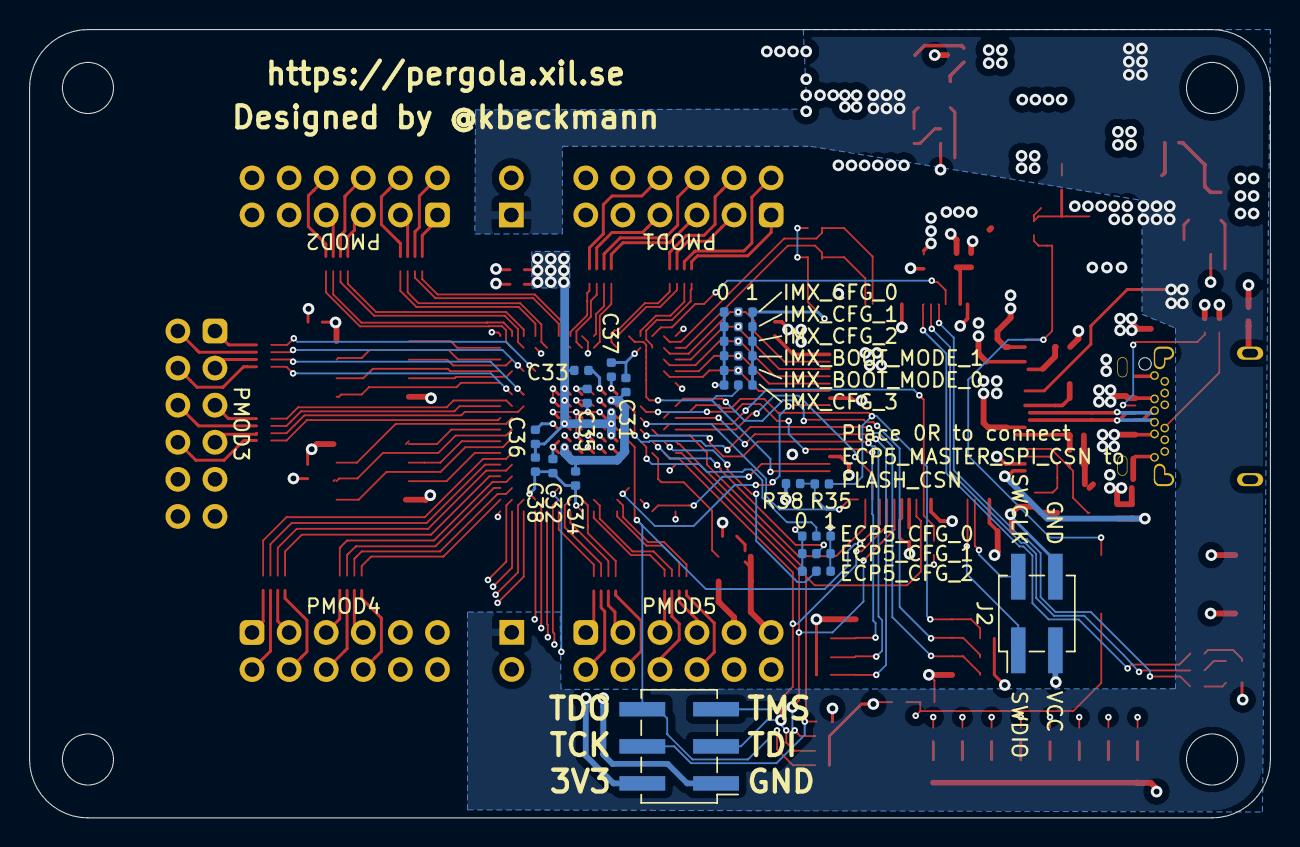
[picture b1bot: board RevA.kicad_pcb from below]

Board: 4 copper layers, 85.0 x 54.0 mm, 148 parts (21 on the bottom side), 175 nets.

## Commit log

2020-06-11 Remove binaries from git
2020-06-11 Upgrade to kicad nightly, including schematic file format
    bak
2020-09-01 Dual source design from Digikey/Mouser, rev 0.2R
    Adjustable Reg -> AP3211KTR-G1 + Freewheel Diode
    Fixed Reg -> AP2120N-2.5TRG1
    24MHz Crystal -> Epson TSX-3225
    16MHz OSC -> ECS-3225MV
    USB Connector -> CUI UJ31-CH-31-SMT-TR
    RGB LED -> Cree CLMVC-FKA
2020-09-01 Add images of rev 0.2R
